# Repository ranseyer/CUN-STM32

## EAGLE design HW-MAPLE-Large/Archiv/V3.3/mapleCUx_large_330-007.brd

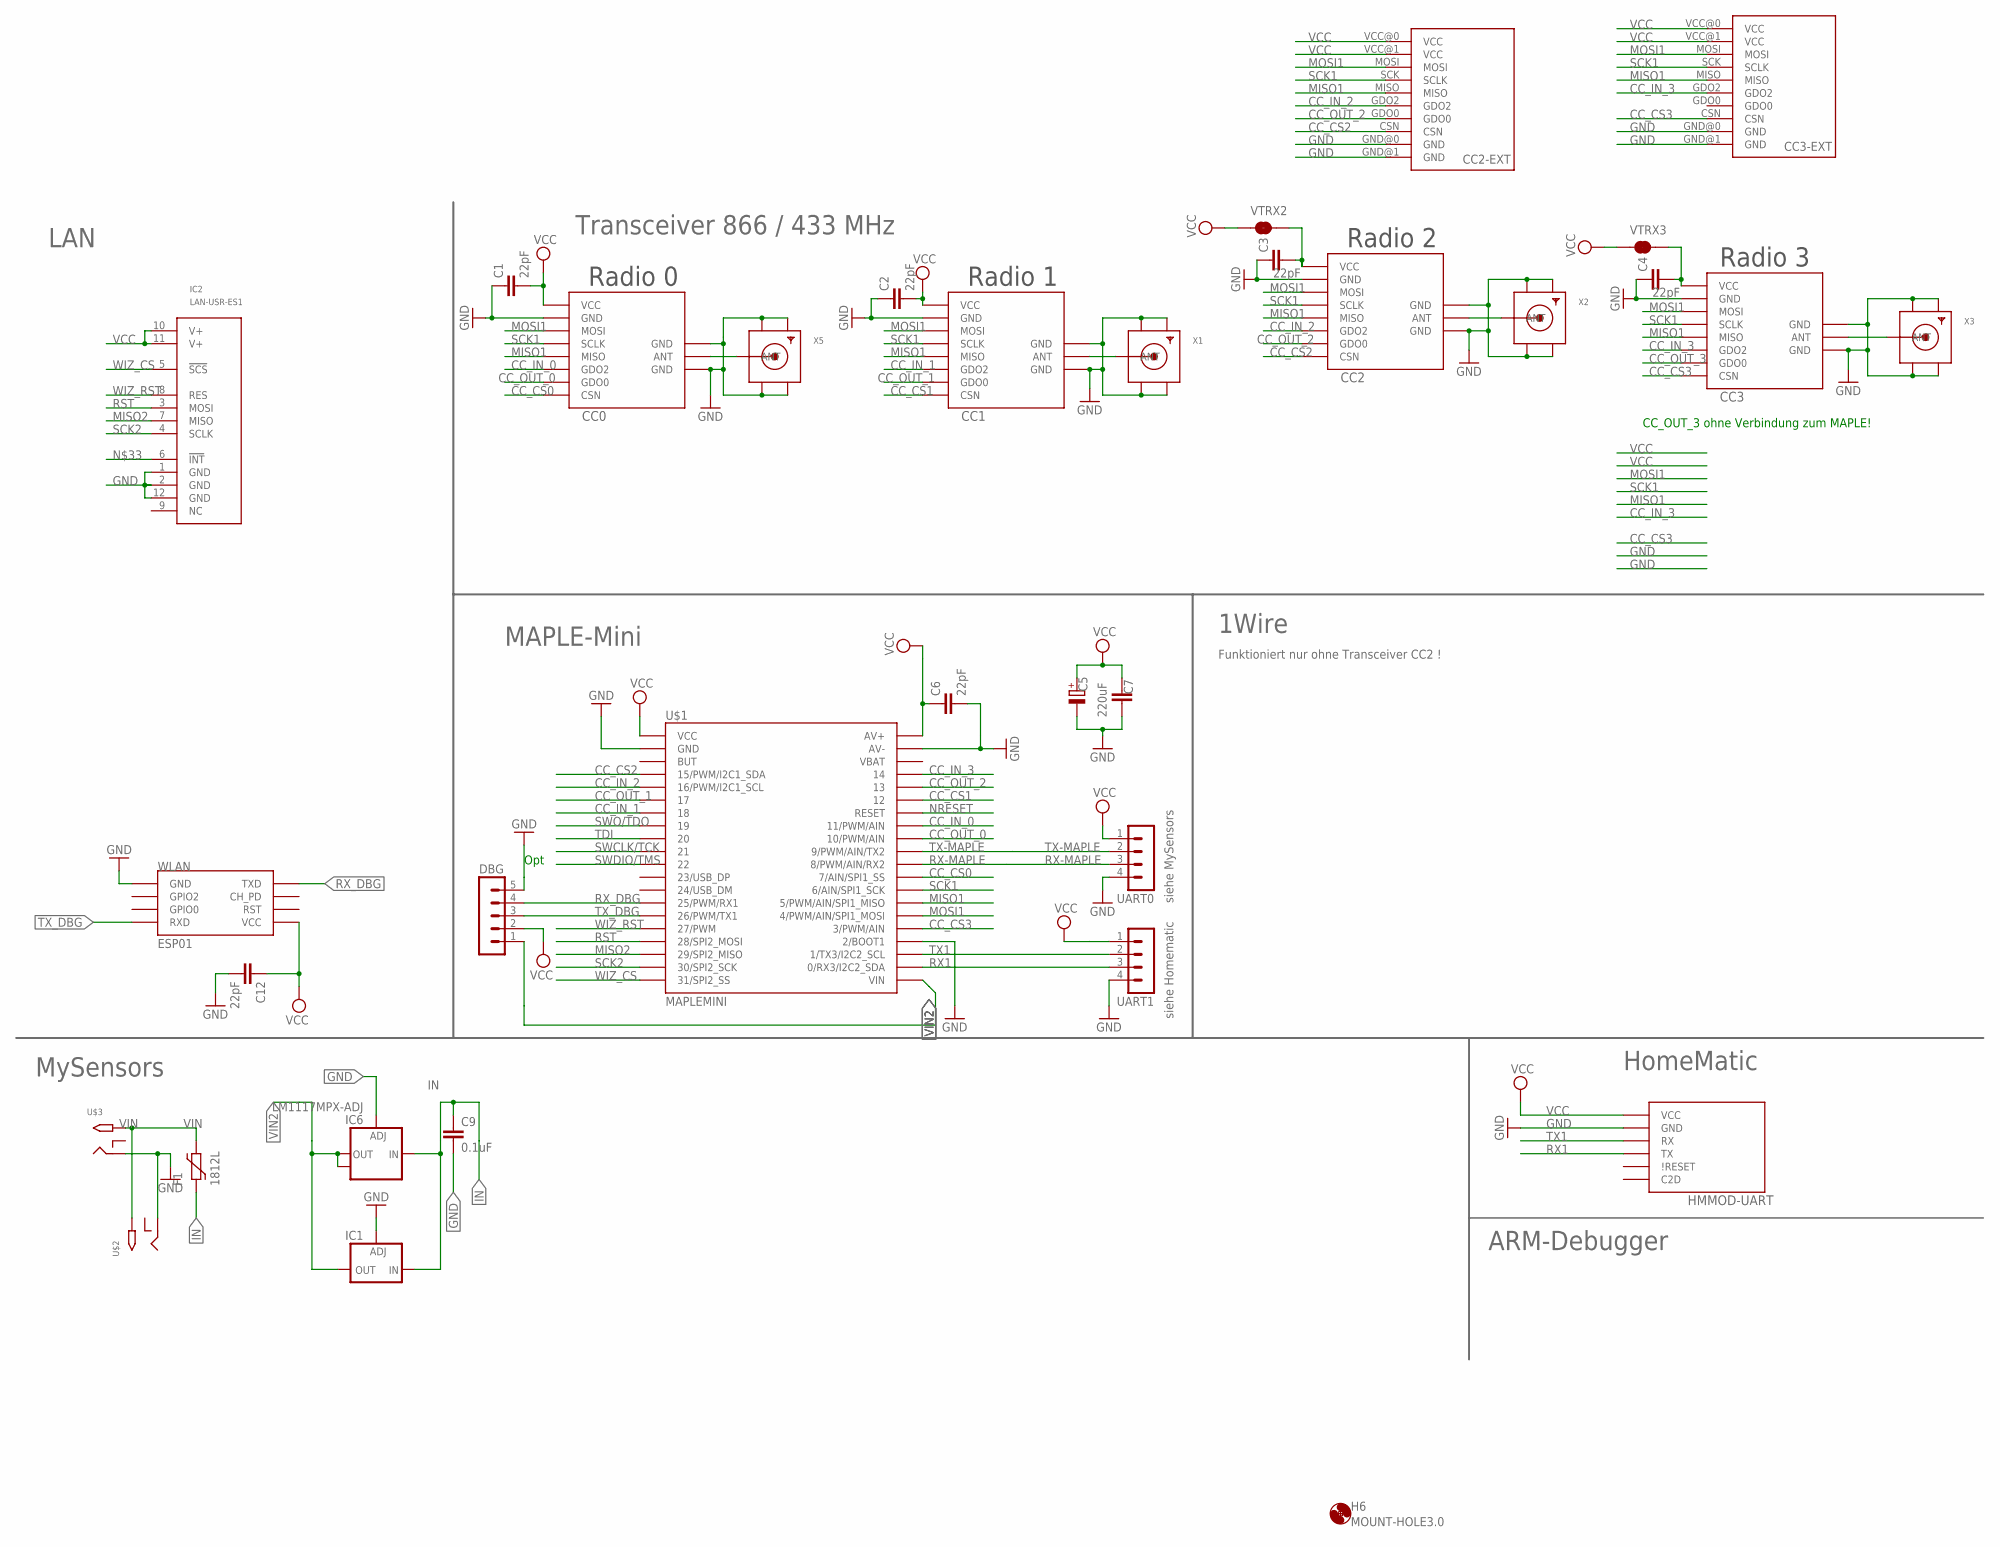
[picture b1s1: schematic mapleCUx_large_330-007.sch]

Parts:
C1, C2, C3, C4, C6, C12: 22pF; C0805
C5: 220uF; E5-8,5
C7: C-EUC1812; C1812
C9: 0.1uF; C1206
CC0: CC1101; CC1101_MODULE1_SMD
CC1, CC2, CC3: CC1101_MODULE1SMD; CC1101_MODULE1_SMD
CC2-EXT, CC3-EXT: CC1101_MODULE3_DIL
DBG: MA05-1
F1: 1812L
H6: MOUNT-HOLE3.0; 3,0
HMMOD-UART: HM-MOD-UARTDIL; HM-MOD-UART-DIL
IC1: LD117ADT50TR; DPACK
IC2: LAN-USR-ES1; USR-ES1
IC6: LM1117MPX-ADJ; SOT223
U$1: MAPLEMINI; 20-DIP
U$2, U$3: 2.1MMJACKTHM; PJ-102A
UART0, UART1: MA04-1
VTRX2, VTRX3: JUMPER-SMT_2_NC_TRACE_SILK; SMT-JUMPER_2_NC_TRACE_SILK
WLAN: ESP01
X1, X2, X3, X5: SMACONNECTOR_EDGE; SMA_EDGELAUNCH

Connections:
ANT0: CC0.ANT, X5.P (ANT)
ANT1: CC1.ANT, X1.P (ANT)
ANT2: CC2.ANT, X2.P (ANT)
ANT3: CC3.ANT, X3.P (ANT)
CC_CS0: CC0.CSN, U$1.29 (7/AIN/SPI1_SS)
CC_CS1: CC1.CSN, U$1.35 (12)
CC_CS2: CC2.CSN, CC2-EXT.CSN, U$1.4 (15/PWM/I2C1_SDA)
CC_CS3: CC3.CSN, CC3-EXT.CSN, U$1.25 (3/PWM/AIN)
CC_IN_0: CC0.GDO2, U$1.33 (11/PWM/AIN)
CC_IN_1: CC1.GDO2, U$1.7 (18)
CC_IN_2: CC2.GDO2, CC2-EXT.GDO2, U$1.5 (16/PWM/I2C1_SCL)
CC_IN_3: CC3.GDO2, CC3-EXT.GDO2, U$1.37 (14)
CC_OUT_0: CC0.GDO0, U$1.32 (10/PWM/AIN)
CC_OUT_1: CC1.GDO0, U$1.6 (17)
CC_OUT_2: CC2.GDO0, CC2-EXT.GDO0, U$1.36 (13)
CC_OUT_3: CC3.GDO0
GND: C1.1, C2.1, C3.1, C4.1, C5.-, C6.2, C7.1, C9.2, C12.2, CC0.GND@0 (GND), CC0.GND@1 (GND), CC0.GND@2 (GND), CC1.GND@0 (GND), CC1.GND@1 (GND), CC1.GND@2 (GND), CC2.GND@0 (GND), CC2.GND@1 (GND), CC2.GND@2 (GND), CC2-EXT.GND@0 (GND), CC2-EXT.GND@1 (GND), CC3.GND@0 (GND), CC3.GND@1 (GND), CC3.GND@2 (GND), CC3-EXT.GND@0 (GND), CC3-EXT.GND@1 (GND), DBG.5, HMMOD-UART.2 (GND), IC1.1 (ADJ), IC2.1 (GND), IC2.2 (GND), IC2.12 (GND), IC6.1 (ADJ), U$1.2 (GND), U$1.24 (2/BOOT1), U$1.39 (AV-), U$2.RING, U$3.RING, UART0.4, UART1.4, WLAN.GND, X1.GND@1 (GND4), X1.GND@2 (GND3), X1.GND@3 (GND2), X1.GND@4 (GND1), X2.GND@1 (GND4), X2.GND@2 (GND3), X2.GND@3 (GND2), X2.GND@4 (GND1), X3.GND@1 (GND4), X3.GND@2 (GND3), X3.GND@3 (GND2), X3.GND@4 (GND1), X5.GND@1 (GND4), X5.GND@2 (GND3), X5.GND@3 (GND2), X5.GND@4 (GND1)
IN: C9.1, F1.P$1 (1), IC1.3 (IN), IC6.3 (IN)
MISO1: CC0.MISO, CC1.MISO, CC2.MISO, CC2-EXT.MISO, CC3.MISO, CC3-EXT.MISO, U$1.27 (5/PWM/AIN/SPI1_MISO)
MISO2: IC2.7 (MISO), U$1.18 (29/SPI2_MISO)
MOSI1: CC0.MOSI, CC1.MOSI, CC2.MOSI, CC2-EXT.MOSI, CC3.MOSI, CC3-EXT.MOSI, U$1.26 (4/PWM/AIN/SPI1_MOSI)
unnamed: C3.2, CC2.VCC, VTRX2.2
unnamed: C4.2, CC3.VCC, VTRX3.2
NRESET: U$1.34 (RESET)
RST: IC2.3 (MOSI), U$1.17 (28/SPI2_MOSI)
RX1: HMMOD-UART.5 (TX), U$1.22 (0/RX3/I2C2_SDA), UART1.3
RX-MAPLE: U$1.30 (8/PWM/AIN/RX2), UART0.3
RX_DBG: DBG.4, U$1.14 (25/PWM/RX1), WLAN.TX (TXD)
SCK1: CC0.SCLK, CC1.SCLK, CC2.SCLK, CC2-EXT.SCK (SCLK), CC3.SCLK, CC3-EXT.SCK (SCLK), U$1.28 (6/AIN/SPI1_SCK)
SCK2: IC2.4 (SCLK), U$1.19 (30/SPI2_SCK)
SWCLK/TCK: U$1.10 (21)
SWDIO/TMS: U$1.11 (22)
SWO/TDO: U$1.8 (19)
TDI: U$1.9 (20)
TX1: HMMOD-UART.6 (RX), U$1.23 (1/TX3/I2C2_SCL), UART1.2
TX-MAPLE: U$1.31 (9/PWM/AIN/TX2), UART0.2
TX_DBG: DBG.3, U$1.15 (26/PWM/TX1), WLAN.RX (RXD)
VCC: C1.2, C2.2, C5.+, C6.1, C7.2, C12.1, CC0.VCC, CC1.VCC, CC2-EXT.VCC@0 (VCC), CC2-EXT.VCC@1 (VCC), CC3-EXT.VCC@0 (VCC), CC3-EXT.VCC@1 (VCC), DBG.2, HMMOD-UART.1 (VCC), IC2.10 (V+), IC2.11 (V+), U$1.1 (VCC), U$1.40 (AV+), UART0.1, UART1.1, VTRX2.1, VTRX3.1, WLAN.VCC
VIN: F1.P$2 (2), U$2.TIP, U$3.TIP
VIN2: DBG.1, IC1.4 (OUT), IC6.2 (OUT), IC6.TAB (OUT1), U$1.21 (VIN)
WIZ_CS: IC2.5 (!SCS!), U$1.20 (31/SPI2_SS)
WIZ_RST: IC2.8 (RES), U$1.16 (27/PWM)

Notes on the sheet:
Radio 1
Radio 0
Opt
Radio 2
Radio 3
siehe Homematic
siehe MySensors
1Wire
MySensors
HomeMatic
MAPLE-Mini
Transceiver 866 / 433 MHz
LAN
Funktioniert nur ohne Transceiver CC2 !
ARM-Debugger
CC_OUT_3 ohne Verbindung zum MAPLE!

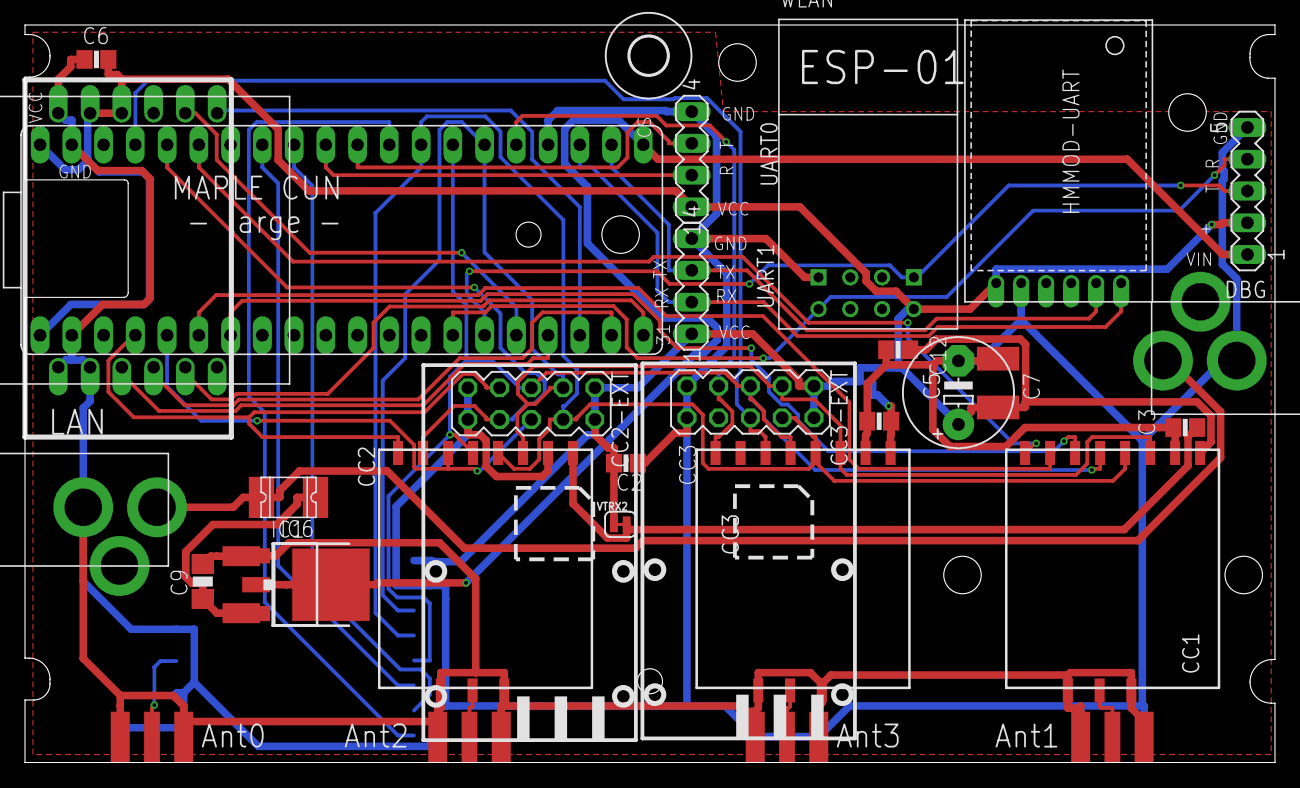
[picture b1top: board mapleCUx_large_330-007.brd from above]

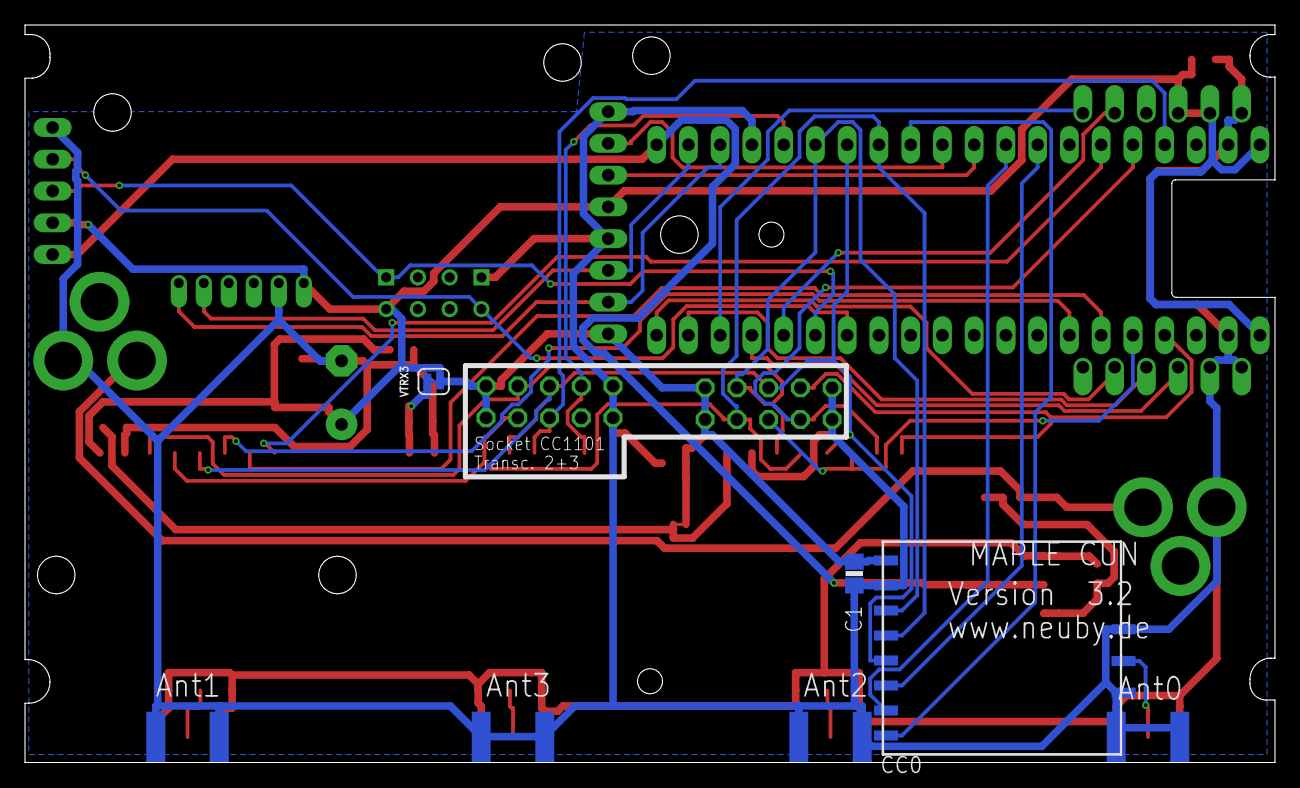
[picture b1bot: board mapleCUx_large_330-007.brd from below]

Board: 2 copper layers, 100.0 x 59.0 mm, 34 parts (3 on the bottom side), 36 nets.

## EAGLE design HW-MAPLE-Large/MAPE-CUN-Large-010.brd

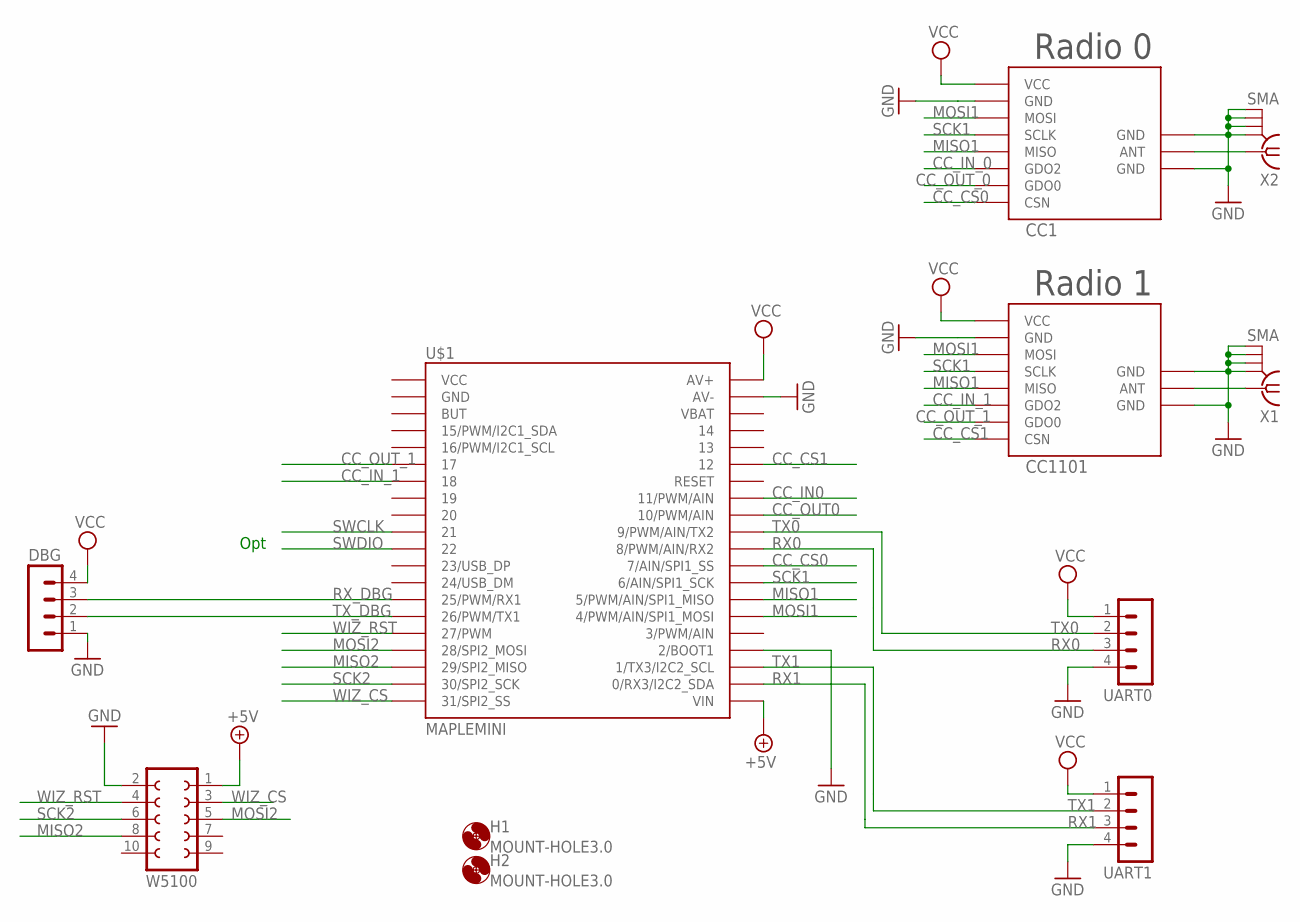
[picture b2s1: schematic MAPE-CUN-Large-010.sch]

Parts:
CC1, CC1101: CC1101_MODULE1SMD; CC1101_MODULE1_SMD
DBG: MA04-1
H1, H2: MOUNT-HOLE3.0; 3,0
U$1: MAPLEMINI; 20-DIP
UART0, UART1: MA04-1
W5100: FE05-2
X1, X2: SMA

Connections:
+5V: U$1.21 (VIN), W5100.1
CC_CS0: CC1.CSN, U$1.29 (7/AIN/SPI1_SS)
CC_CS1: CC1101.CSN, U$1.35 (12)
CC_IN0: U$1.33 (11/PWM/AIN)
CC_IN_0: CC1.GDO2
CC_IN_1: CC1101.GDO2, U$1.7 (18)
CC_OUT0: U$1.32 (10/PWM/AIN)
CC_OUT_0: CC1.GDO0
CC_OUT_1: CC1101.GDO0, U$1.6 (17)
GND: CC1.GND@0 (GND), CC1.GND@1 (GND), CC1.GND@2 (GND), CC1101.GND@0 (GND), CC1101.GND@1 (GND), CC1101.GND@2 (GND), DBG.1, U$1.24 (2/BOOT1), U$1.39 (AV-), UART0.4, UART1.4, W5100.2, X1.GND@1 (2), X1.GND@2 (3), X1.GND@3 (4), X1.GND@4 (5), X2.GND@1 (2), X2.GND@2 (3), X2.GND@3 (4), X2.GND@4 (5)
MISO1: CC1.MISO, CC1101.MISO, U$1.27 (5/PWM/AIN/SPI1_MISO)
MISO2: U$1.18 (29/SPI2_MISO), W5100.8
MOSI1: CC1.MOSI, CC1101.MOSI, U$1.26 (4/PWM/AIN/SPI1_MOSI)
MOSI2: U$1.17 (28/SPI2_MOSI), W5100.5
unnamed: CC1101.ANT, X1.1
unnamed: CC1.ANT, X2.1
RX0: U$1.30 (8/PWM/AIN/RX2), UART0.3
RX1: U$1.22 (0/RX3/I2C2_SDA), UART1.3
RX_DBG: DBG.3, U$1.14 (25/PWM/RX1)
SCK1: CC1.SCLK, CC1101.SCLK, U$1.28 (6/AIN/SPI1_SCK)
SCK2: U$1.19 (30/SPI2_SCK), W5100.6
SWCLK: U$1.10 (21)
SWDIO: U$1.11 (22)
TX0: U$1.31 (9/PWM/AIN/TX2), UART0.2
TX1: U$1.23 (1/TX3/I2C2_SCL), UART1.2
TX_DBG: DBG.2, U$1.15 (26/PWM/TX1)
VCC: CC1.VCC, CC1101.VCC, DBG.4, U$1.40 (AV+), UART0.1, UART1.1
WIZ_CS: U$1.20 (31/SPI2_SS), W5100.3
WIZ_RST: U$1.16 (27/PWM), W5100.4

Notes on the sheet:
Radio 1
Radio 0
Opt

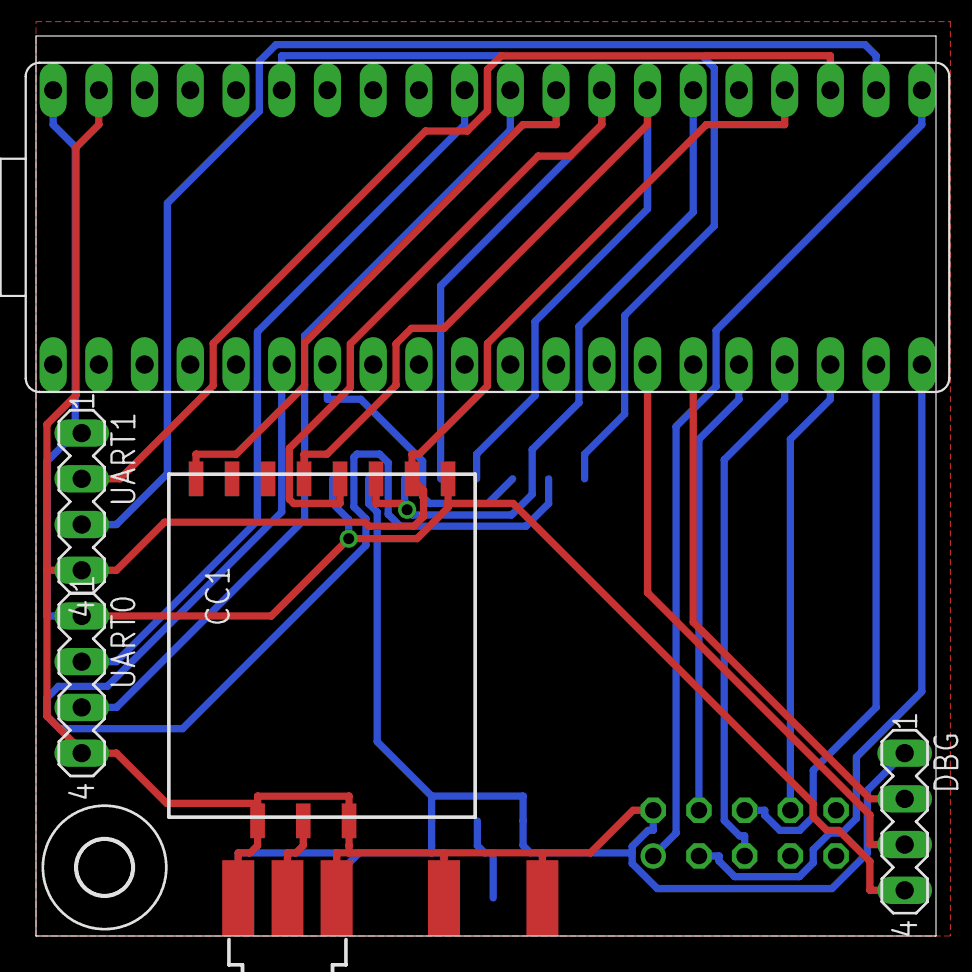
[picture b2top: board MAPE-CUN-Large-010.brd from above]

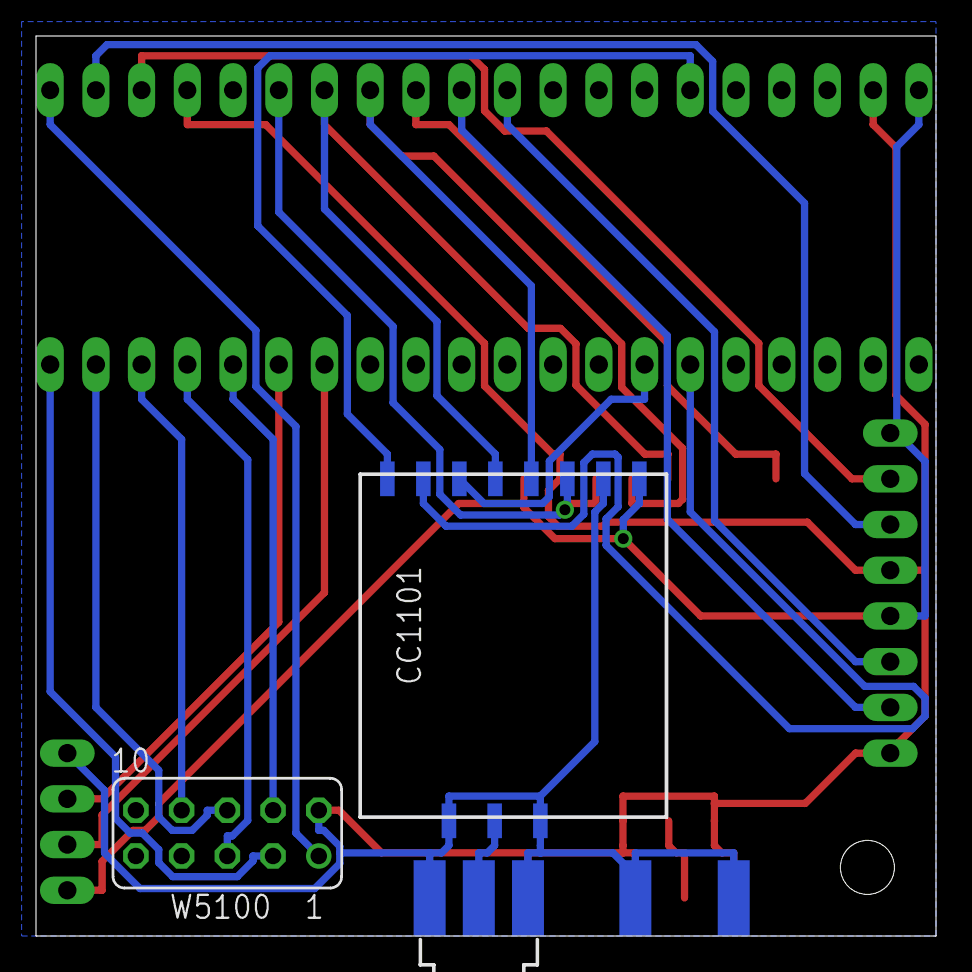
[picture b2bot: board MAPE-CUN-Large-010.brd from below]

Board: 2 copper layers, 50.0 x 50.0 mm, 11 parts (3 on the bottom side), 23 nets.

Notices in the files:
parts and their libraries:
SparkFun-Jumpers: Licensing: Creative Commons ShareAlike 4.0 International - https://creativecommons.org/licenses/by-sa/4.0
